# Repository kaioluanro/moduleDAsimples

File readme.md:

# Module D/A signal audio

Hi, it's project the module for input/output signal to computer signal.

# Features

- 5V or 3.3v power supply;
- ADC: 24bit;
- Frequence samples ADC max: 128;
- DAC: 24bit or 32bit;
- Frequence samples DAC max: 64;
- Stereo Input signal audio;
- Stereo Output signal audio;
- Connection  via i2s;

## Application 

Used for signal the audio purpose.

## Function Diagram
```mermaid
sequenceDiagram
INPUT ->> ADC: Signal
ADC->>PROCESS: 24-bits
Note over PROCESS: Process signal digital.
PROCESS->> DAC: 24-bits or 32-bits
DAC->> OUTPUT: Signal

```

## Alert
module still in test and subject to change.

## I2S for Blackpill(STM32F411CEU6)
The STMicroelectronics provides an documention know emulation I2S used SPI and TIMER. overview in the link [Emulation I2S](https://www.st.com/resource/en/application_note/an5086-i2s-protocol-emulation-on-stm32l0-series-microcontrollers-using-a-standard-spi-peripheral-stmicroelectronics.pdf).

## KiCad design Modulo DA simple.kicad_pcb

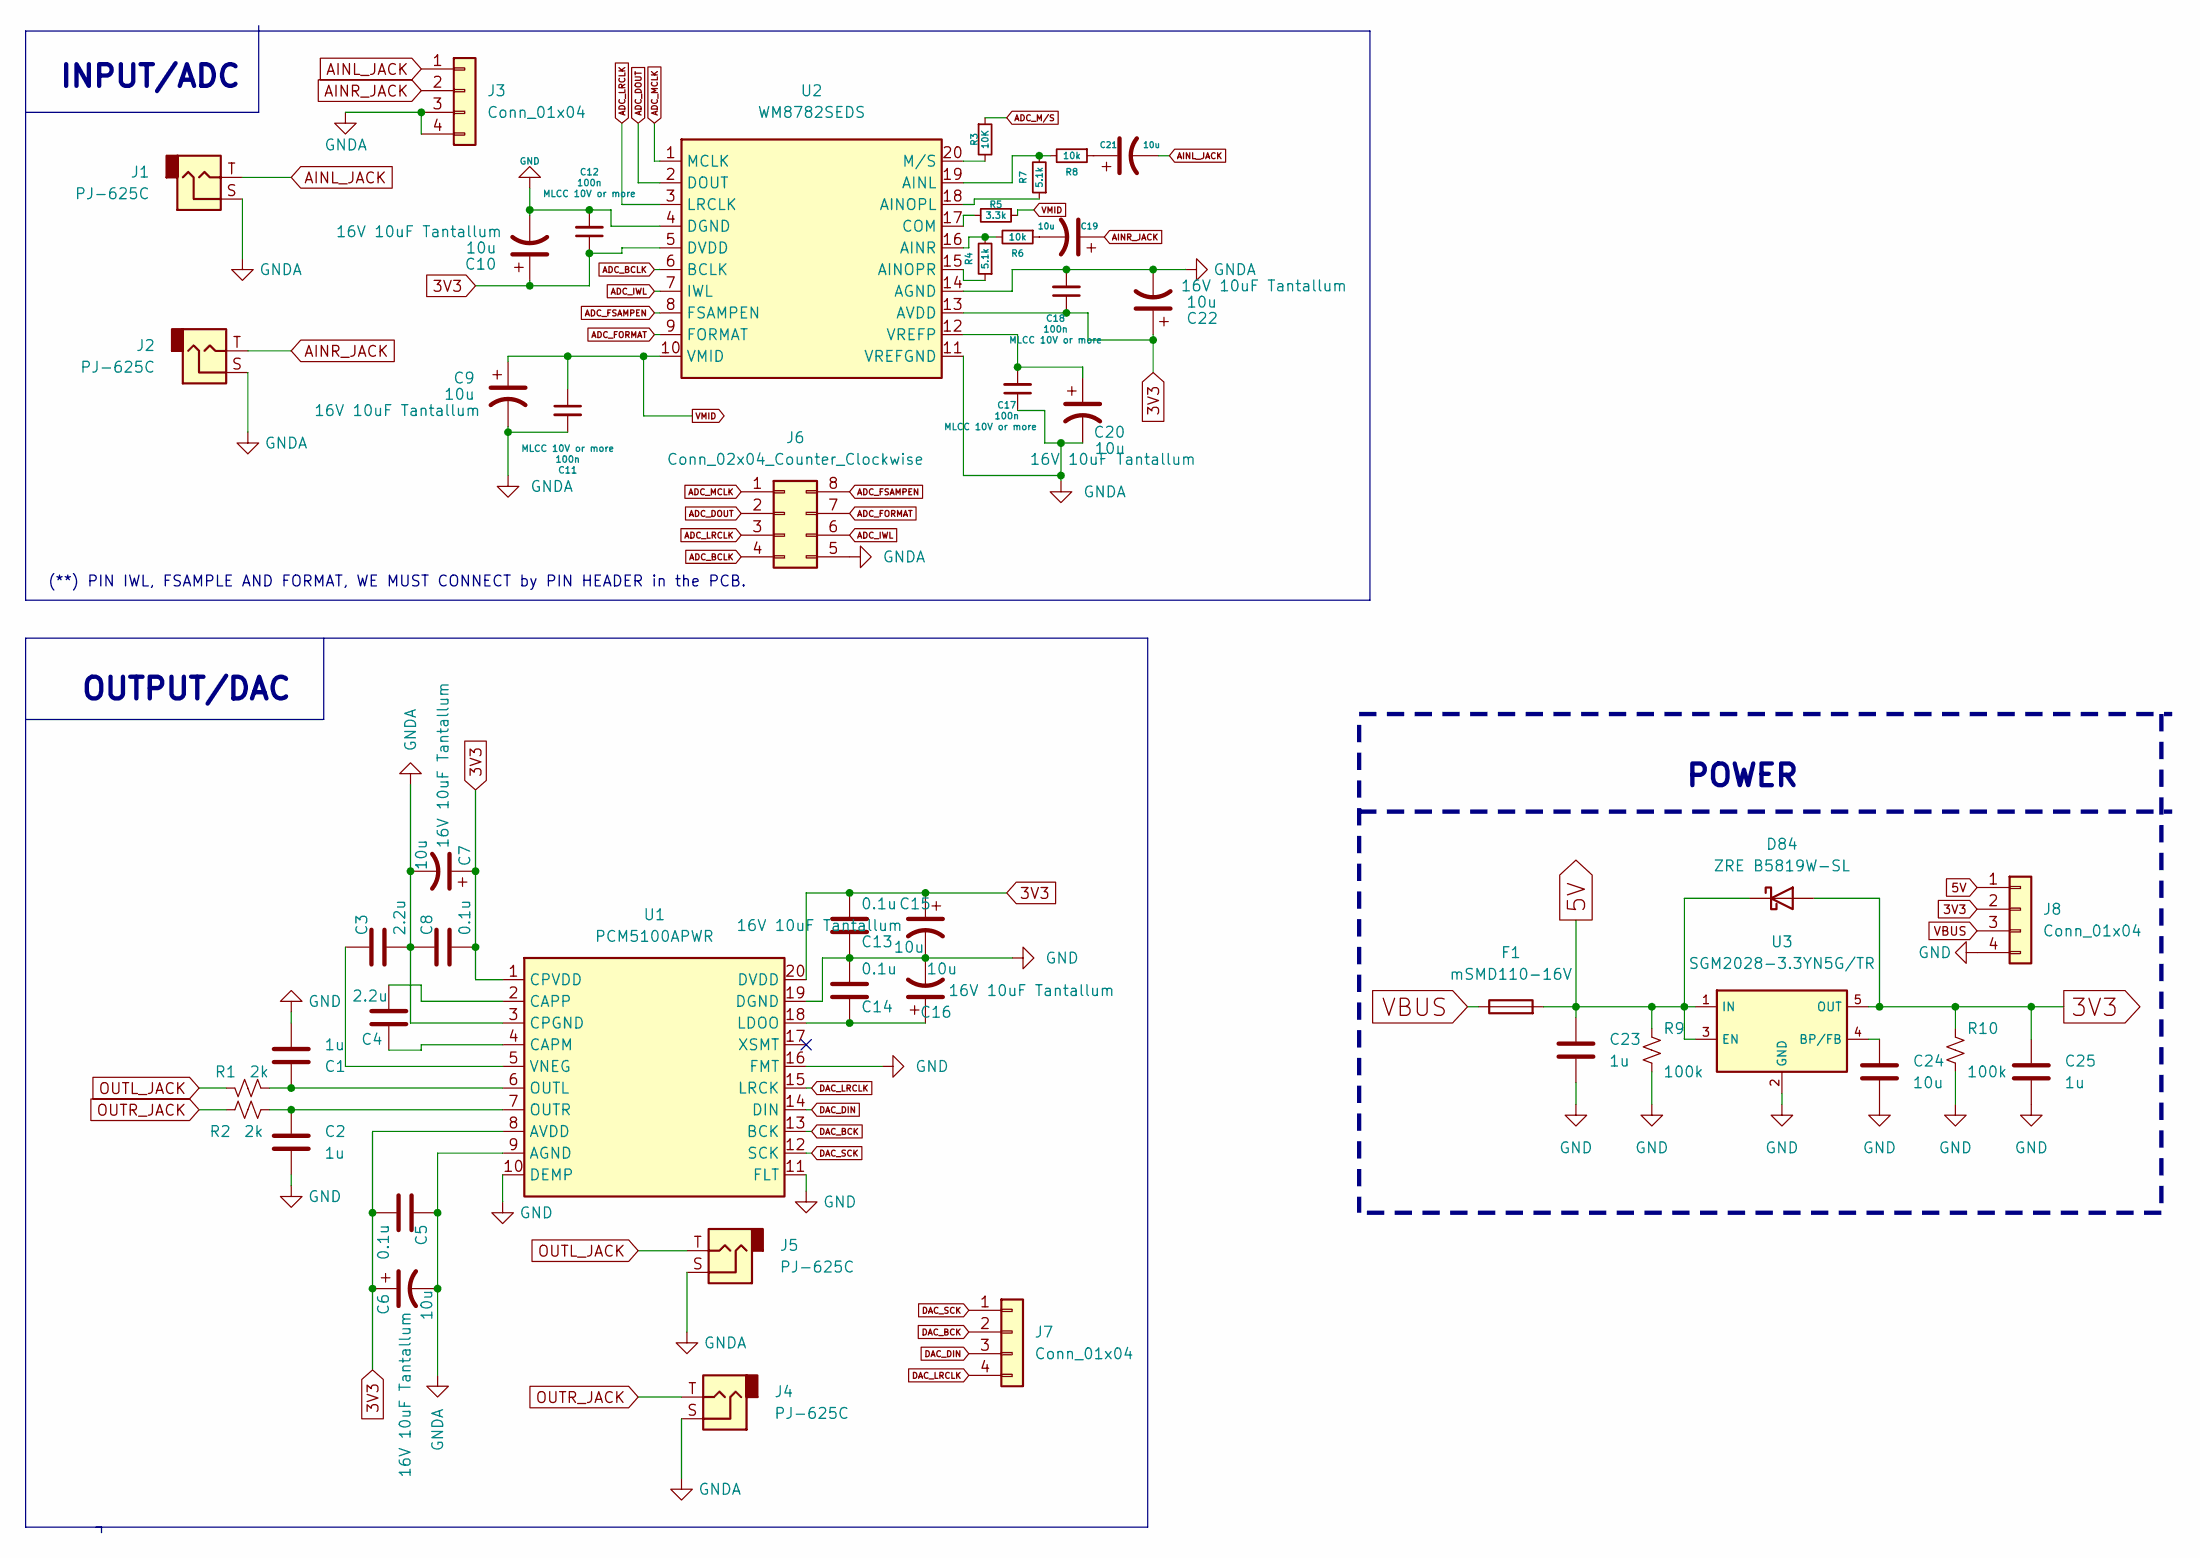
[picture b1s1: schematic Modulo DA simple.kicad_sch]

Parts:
C1, C2, C23, C25: 1u; C_0603_1608Metric; Manufacturer Part Number 0603F105M160NT; LCSC Part # C1689
C3, C4: 2.2u; C_0603_1608Metric; Manufacturer Part Number CL10A225KB8NNNC; LCSC Part # C913904
C5, C8, C13, C14: 0.1u; C_0805_2012Metric; Manufacturer Part Number UMK107AB7105KA-T; LCSC Part # C126469
C6, C7, C9, C10, C15, C16, C19, C20, C21, C22: 10u; CP_EIA-3216-18_Kemet-A; Manufacturer Part Number TAJA106K016RNJ; LCSC Part # C7171
C11, C12, C17, C18: 100n; C_0603_1608Metric; Manufacturer Part Number 0603B104K160CT; LCSC Part # C80516
C24: 10u; C_1210_3225Metric; Manufacturer Part Number EMK325BJ106KN-T; LCSC Part # C92769
D84: ZRE B5819W-SL; D_SOD-123; Manufacturer Part Number B5819W-SL; LCSC Part # C779676
F1: mSMD110-16V; C_1812_4532Metric; Manufacturer Part Number mSMD110-16V; LCSC Part # C69691
J1, J2, J4, J5: PJ-625C; Jack_6.35mm_Neutrik_NMJ6HFD2-AU_Horizontal; Manufacturer Part Number PJ-625C; LCSC Part # C309291
J3, J7, J8: Conn_01x04; PinHeader_1x04_P1.27mm_Horizontal; Manufacturer Part Number DZ127R-11-04-25; LCSC Part # C2935944
J6: Conn_02x04_Counter_Clockwise; PinHeader_2x04_P1.27mm_Horizontal; Manufacturer Part Number PZ127V-12-08-0720; LCSC Part # C541878
R1, R2: 2k; R_0805_2012Metric; Manufacturer Part Number RMC08052K1%N; LCSC Part # C269745
R3: 10K; R_0603_1608Metric; Manufacturer Part Number RC0603JR-0710KL; LCSC Part # C99198
R4, R7: 5.1k; R_0603_1608Metric; Manufacturer Part Number RS-03K5101FT; LCSC Part # C156350
R5: 3.3k; R_0603_1608Metric; Manufacturer Part Number RS-03K332JT; LCSC Part # C72816
R6, R8: 10k; R_0603_1608Metric; Manufacturer Part Number RC0603JR-0710KL; LCSC Part # C99198
R9, R10: 100k; R_0603_1608Metric; Manufacturer Part Number RC0603FR-07100KL; LCSC Part # C14675
U1: PCM5100APWR; TSSOP-20_4.4x6.5mm_P0.65mm; Manufacturer Part Number PCM5100APWR; LCSC Part # C131154
U2: WM8782SEDS; SSOP-20_5.3x7.2mm_P0.65mm; Manufacturer Part Number WM8782SEDS; LCSC Part # C323842
U3: SGM2028-3.3YN5G/TR; SOT-23-5; Manufacturer Part Number SGM2028-3.3YN5G/TR; LCSC Part # C81088

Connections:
3V3: C5.2, C6.1, C7.1, C8.2, C10.1, C12.1, C13.2, C15.1, C18.1, C22.1, C25.1, D84.2 (A), J8.2, R10.1, U1.1 (CPVDD), U1.8 (AVDD), U1.20 (DVDD), U2.5 (DVDD), U2.13 (AVDD), U3.5 (OUT)
5V: C23.1, D84.1 (K), F1.2, J8.1, R9.1, U3.1 (IN), U3.3 (EN); also elsewhere on the board
ADC_BCLK: J6.4, U2.6 (BCLK)
ADC_DOUT: J6.2, U2.2 (DOUT)
ADC_FORMAT: J6.7, U2.9 (FORMAT)
ADC_FSAMPEN: J6.8, U2.8 (FSAMPEN)
ADC_IWL: J6.6, U2.7 (IWL)
ADC_LRCLK: J6.3, U2.3 (LRCLK)
ADC_MCLK: J6.1, U2.1 (MCLK)
ADC_M/S: R3.1
AINL_JACK: C21.2, J1.T, J3.1
AINR_JACK: C19.1, J2.T, J3.2
DAC_BCK: J7.2, U1.13 (BCK)
DAC_DIN: J7.3, U1.14 (DIN)
DAC_LRCLK: J7.4, U1.15 (LRCK)
DAC_SCK: J7.1, U1.12 (SCK)
GND: C1.2, C2.2, C10.2, C12.2, C13.1, C14.2, C15.2, C16.2, C23.2, C24.2, C25.2, J8.4, R9.2, R10.2, U1.10 (DEMP), U1.11 (FLT), U1.16 (FMT), U1.19 (DGND), U2.4 (DGND), U3.2 (GND)
GNDA: C3.2, C5.1, C6.2, C7.2, C8.1, C9.2, C11.2, C17.1, C18.2, C20.2, C22.2, J1.S, J2.S, J3.3, J3.4, J4.S, J5.S, J6.5, U1.3 (CPGND), U1.9 (AGND), U2.11 (VREFGND), U2.14 (AGND)
unnamed: C1.1, R1.2, U1.6 (OUTL)
unnamed: C2.1, R2.2, U1.7 (OUTR)
unnamed: C3.1, U1.5 (VNEG)
unnamed: C4.1, U1.4 (CAPM)
unnamed: C4.2, U1.2 (CAPP)
unnamed: C14.1, C16.1, U1.18 (LDOO)
unnamed: C17.2, C20.1, U2.12 (VREFP)
unnamed: C19.2, R6.1
unnamed: C21.1, R8.1
unnamed: C24.1, U3.4 (BP/FB)
unnamed: R3.2, U2.20 (M/S)
unnamed: R4.1, U2.15 (AINOPR)
unnamed: R4.2, R6.2, U2.16 (AINR)
unnamed: R5.2, U2.17 (COM)
unnamed: R7.1, U2.18 (AINOPL)
unnamed: R7.2, R8.2, U2.19 (AINL)
OUTL_JACK: J5.T, R1.1
OUTR_JACK: J4.T, R2.1
VBUS: F1.1, J8.3; also elsewhere on the board
VMID: C9.1, C11.1, R5.1, U2.10 (VMID)

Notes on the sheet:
OUTPUT/DAC
POWER
(**) PIN IWL, FSAMPLE AND FORMAT, WE MUST CONNECT by PIN HEADER in the PCB.
INPUT/ADC

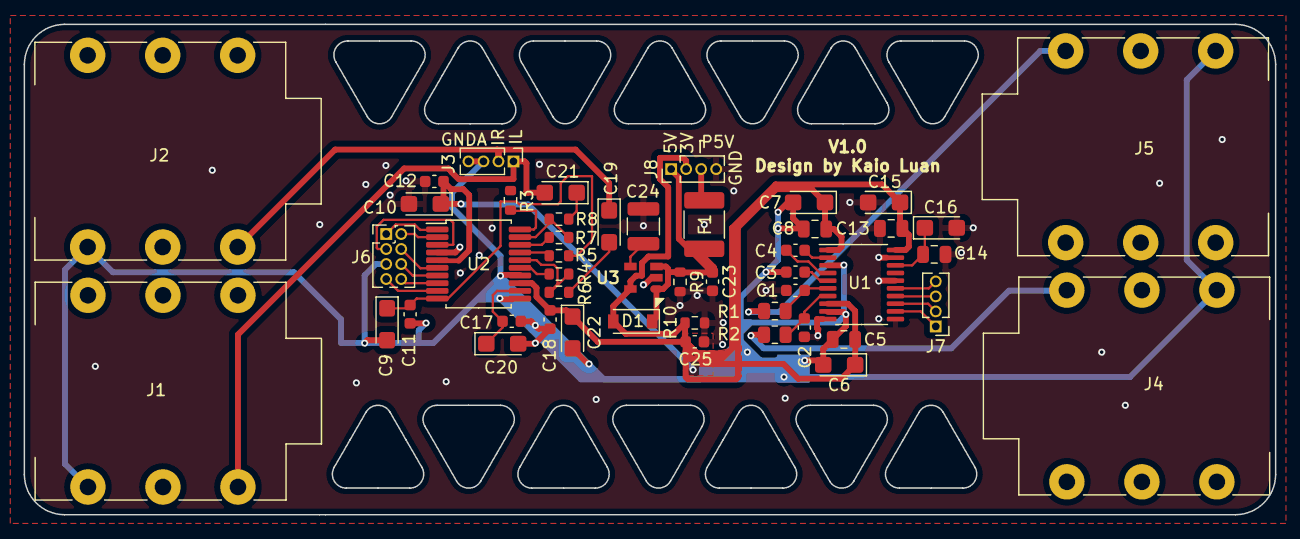
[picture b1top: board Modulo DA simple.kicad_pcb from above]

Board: 2 copper layers, 105.9 x 41.5 mm, 48 parts (0 on the bottom side), 37 nets.

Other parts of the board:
F?: mSMD110-16V; C_1812_4532Metric

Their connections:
5V: F?.2; also elsewhere on the board
VBUS: F?.1; also elsewhere on the board

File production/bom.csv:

Designator,Footprint,Quantity,Value,LCSC Part #
C11,C_0603_1608Metric,1,100n,C80516
J7,PinHeader_1x04_P1.27mm_Vertical,1,Conn_01x04,C2935944
C7,CP_EIA-3216-18_Kemet-A,1,10u,C7171
U1,TSSOP-20_4.4x6.5mm_P0.65mm,1,PCM5100APWR,C131154
C9,CP_EIA-3216-18_Kemet-A,1,10u,C7171
C4,C_0603_1608Metric,1,2.2u,C913904
C16,CP_EIA-3216-18_Kemet-A,1,10u,C7171
J6,PinHeader_2x04_P1.27mm_Vertical,1,Conn_02x04_Counter_Clockwise,C541878
F1,C_1812_4532Metric,1,mSMD110-16V,C69691
C22,CP_EIA-3216-18_Kemet-A,1,10u,C7171
C1,C_0603_1608Metric,1,1u,C1689
J5,Jack_6.35mm_Neutrik_NMJ6HFD2-AU_Horizontal,1,PJ-625C,C309291
J2,Jack_6.35mm_Neutrik_NMJ6HFD2-AU_Horizontal,1,PJ-625C,C309291
R10,R_0603_1608Metric,1,100k,C14675
C17,C_0603_1608Metric,1,100n,C80516
J1,Jack_6.35mm_Neutrik_NMJ6HFD2-AU_Horizontal,1,PJ-625C,C309291
J4,Jack_6.35mm_Neutrik_NMJ6HFD2-AU_Horizontal,1,PJ-625C,C309291
C5,C_0805_2012Metric,1,0.1u,C126469
D1,D_SOD-123,1,ZRE B5819W-SL,C779676
C23,C_0603_1608Metric,1,1u,C1689
C24,C_1210_3225Metric,1,10u,C92769
J3,PinHeader_1x04_P1.27mm_Vertical,1,Conn_01x04,C2935944
C14,C_0805_2012Metric,1,0.1u,C126469
C13,C_0805_2012Metric,1,0.1u,C126469
C20,CP_EIA-3216-18_Kemet-A,1,10u,C7171
R4,R_0603_1608Metric,1,5.1k,C156350
C6,CP_EIA-3216-18_Kemet-A,1,10u,C7171
R1,R_0805_2012Metric,1,2k,C269745
C25,C_0603_1608Metric,1,1u,C1689
R5,R_0603_1608Metric,1,3.3k,C72816
U2,SSOP-20_5.3x7.2mm_P0.65mm,1,WM8782SEDS,C323842
U3,SOT-23-5,1,SGM2028-3.3YN5G/TR,C81088
R3,R_0603_1608Metric,1,10K,C99198
C12,C_0603_1608Metric,1,100n,C80516
R9,R_0603_1608Metric,1,100k,C14675
J8,PinHeader_1x04_P1.27mm_Vertical,1,Conn_01x04,C2935944
C21,CP_EIA-3216-18_Kemet-A,1,10u,C7171
C8,C_0805_2012Metric,1,0.1u,C126469
C2,C_0603_1608Metric,1,1u,C1689
C18,C_0603_1608Metric,1,100n,C80516
R8,R_0603_1608Metric,1,10k,C99198
R2,R_0805_2012Metric,1,2k,C269745
C10,CP_EIA-3216-18_Kemet-A,1,10u,C7171
C19,CP_EIA-3216-18_Kemet-A,1,10u,C7171
R7,R_0603_1608Metric,1,5.1k,C156350
C15,CP_EIA-3216-18_Kemet-A,1,10u,C7171
R6,R_0603_1608Metric,1,10k,C99198
C3,C_0603_1608Metric,1,2.2u,C913904

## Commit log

2022-08-31 banner img
2022-08-31 Banner change
2022-08-31 add gnd and gnda in the pcb
2022-08-31 Boom the lcsc
2022-09-02 01092022
2022-09-02 02092022
    Check and connection some components
2022-09-02 02092022-1
2022-09-02 02092022-2
    Send for plot pcb
